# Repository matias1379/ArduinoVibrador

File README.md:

# Arduino Vibrador

En este repositorio se encuentran los archivos correspondientes al bloque de arduino y vibradores segun colores 

### Carpetas Utiles:

**ArduinoVibrador**: Esta carpeta posee la release 1.0v del codigo. Ha sido simulada y deberia funcionar para recibir un paquete JSON(raspberry) con indicaciones de colores dentro y desempaquetarla para vibrar segun el color

**Codigos Ejemplos**: En esta carpeta estan todos los codigos que nos basamos para entender el funcionamiento de JSON y el modulo HC-05. Estos son codigos con propositos generales

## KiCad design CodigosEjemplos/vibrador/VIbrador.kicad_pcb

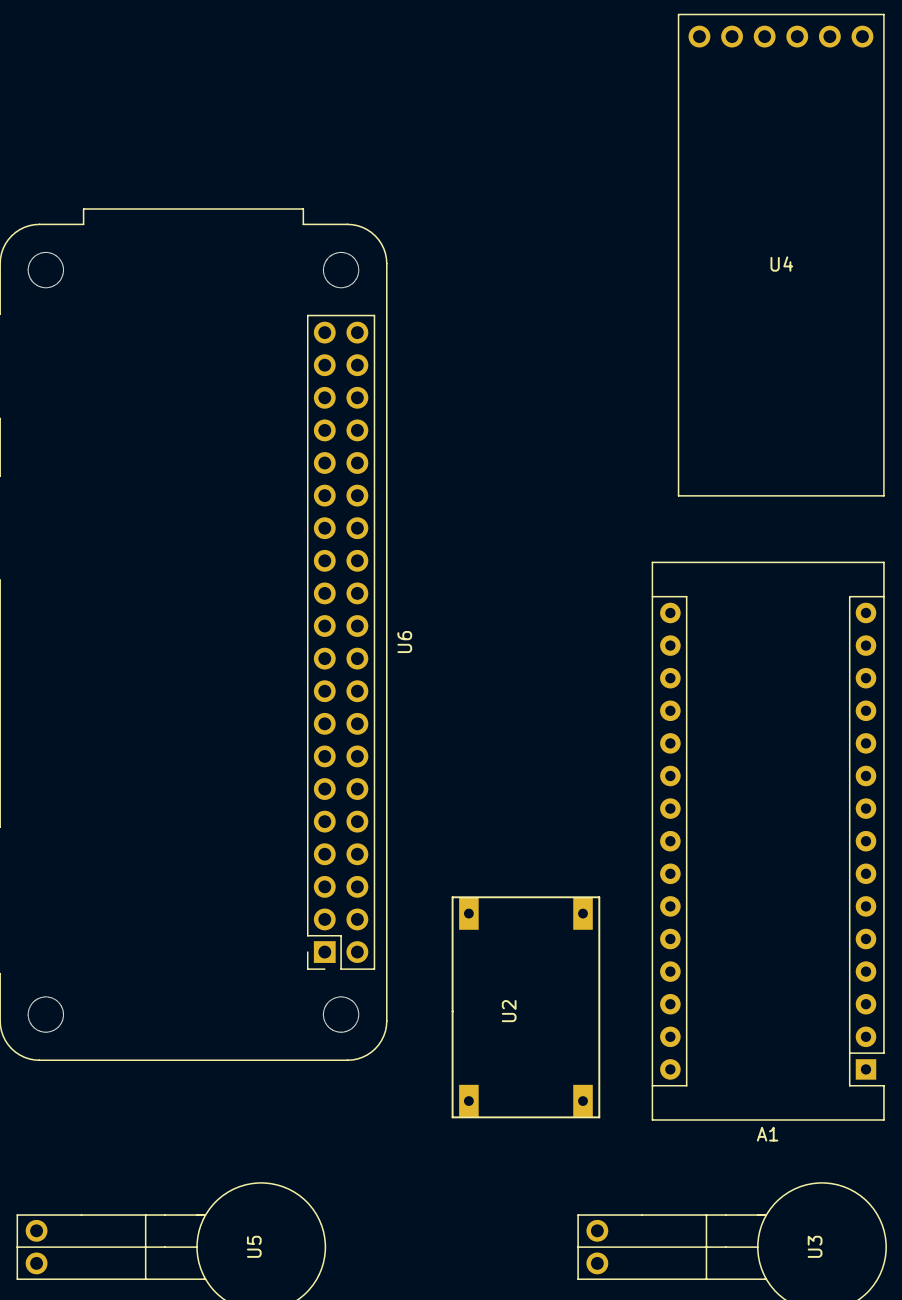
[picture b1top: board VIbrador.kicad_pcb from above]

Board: 2 copper layers, 8 parts (0 on the bottom side), 5 nets, no tracks yet.

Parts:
A1: Arduino_Nano_v3.x; Arduino_Nano
U1, U1#2: Pila3,7V; Pila de Litio
U2: StepDown
U3, U5: Buzzer; Vibrador
U4: HC-05
U6: PiZeroW; Raspberry_Pi_Zero_Socketed_THT_FaceDown_MountingHoles

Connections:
D9: A1.12, U3.1, U5.1
GND: A1.4, A1.29, U3.2, U4.3, U5.2
RX: A1.14, U4.4
TX: A1.13, U4.5
VIN: A1.30, U4.2

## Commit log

2020-03-27 Programas de Json y Bt
2020-03-28 Se ordeno repo
2020-04-04 Los codigos finales se colocaron en ArduinoVibrador que seria los que usemos. Los codigos que ayudan a entender el repo y cada una de sus Features estan dentro de CodigosEjemplos
2020-04-04 se borraron archivos duplicados
2020-04-04 se actualizo el readme
2020-04-05 Se ha realizado el PCB
    Se ha cambiado el esquematico de RX y TX siendo ahora RX el D11 y TX el D10. Se hizo la placa ya que estamos consultando con una empresa para Pcb's flexible
2020-04-05 Agregue un buzzer
2020-04-06 Se agrego informacion al rotulo del pcb
2020-04-06 Se agregó zona de relleno
2020-04-09 Se agrego libreria . cpp y .h de morse
    Se creo para cada color un determinado codigo morse y se hizo un programa de prueba
2020-04-09 Se cambio el archivo .cpp a .c
    Se cambio la extension y el codigo para C(no anda todavia)
2020-04-09 Se ordeno
2020-04-10 Se agrego esquematico de la Pi Zero W
2020-04-11 Se agregaron los PCB de HC-05, pila (falta completar) y vibrador
    Tambien cambie el simbolo de hc-05 ya que le faltaban dos pines
2020-04-11 Se actualizo la poscion de la raspberry para conveniencia de la pi camera
2020-04-13 PCB con StepDown
2020-04-13 Se cambio la extension de.c a .cpp
    Cambiando la extension se logro que ande el programa
2020-04-13 Esquematico
2020-04-14 Se finalizo PCB
    Se cambio la huella de pila, y posicion de rx y tx en arduino
2020-04-14 Ordenar
2020-04-14 Se guardo el PCB finallizado
2020-04-14 Se unieron IN- Y OUT- ya que los dos son GND de el step down y es lo mismo
2020-04-15 Se agregaron las librerias de morse al programa final y sus comparaciones
    Se ha actualizado el programa final
2020-04-24 Se creo la carpeta para el case
2020-04-24 Se inicio el diseño 3D de el case y se modifico el TX/RX del bt para conectarlo a la raspberry
2020-04-26 Se termino el case falta hacerle el hueco dela bateria
2020-04-26 Se termino de hacer las cosas en 3D
    Se creo el case que tiene dos stl:
    Case parte 1 es la base donde van las cosas.
    Case parte 2 es la tapa que tiene el logo y el slogan en braille
2020-04-27 Se borro un error
    habia un punto en el aire en el case
2020-04-27 Correcion de case_placa_parte_1
    El archivo stl estaba desactualizado con respecto a las modificaciones del cad
2020-05-03 Se corrigieron errores y agregaron algunos detalles
    Se hizo un programa para que se pueda escribir en el serial un color y se mande al receptor y vibre de acuerdo al color
